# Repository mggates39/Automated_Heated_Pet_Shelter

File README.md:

# Automated Heated Pet Shelter #
This project is the software to control a heated pet shelter for my cat.

It uses an Uno, a couple of tempearture sensors, a load cell and amplifier, and a relay to activate a heating pad in the bottom of the shelter.

It uses the MyDelay Arduino library found [here](https://github.com/mggates39/MyDelay) on GitHub

Added a KiCad design for an Arduino Uno shield to interface to the sensors and relay.

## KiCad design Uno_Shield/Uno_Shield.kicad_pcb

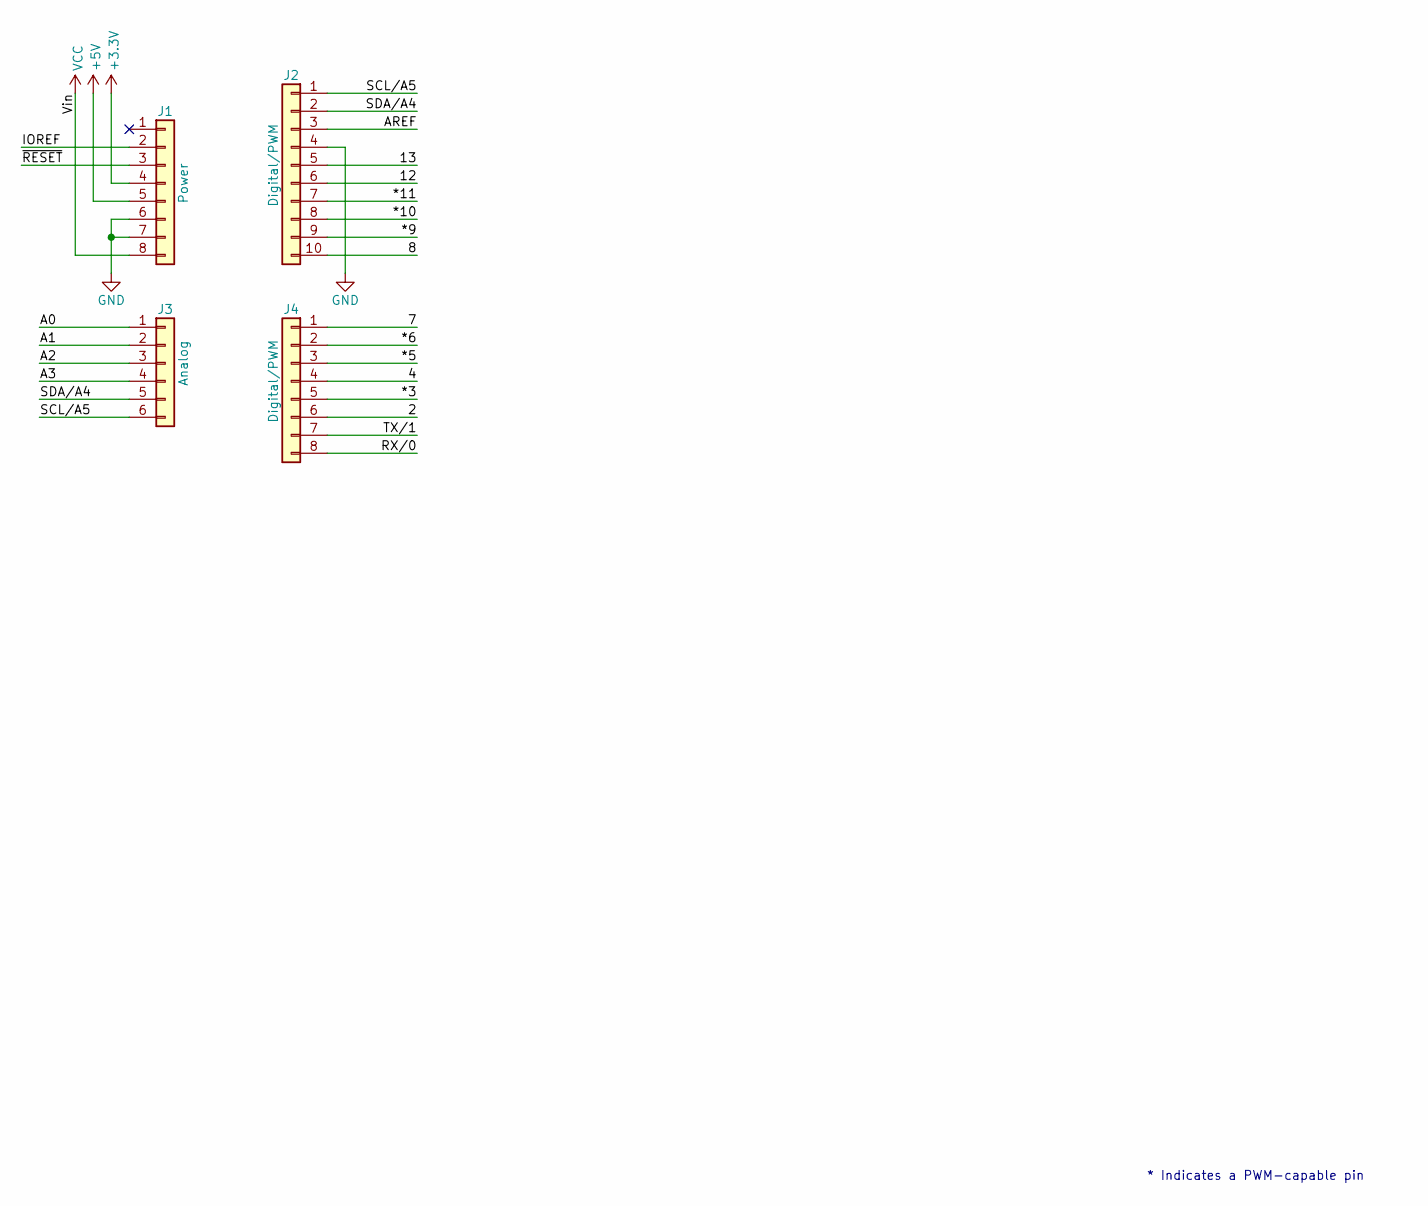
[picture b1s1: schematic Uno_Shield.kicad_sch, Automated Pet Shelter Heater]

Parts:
J1: Power; PinSocket_1x08_P2.54mm_Vertical
J2: Digital/PWM; PinSocket_1x10_P2.54mm_Vertical
J3: Analog; PinSocket_1x06_P2.54mm_Vertical
J4: Digital/PWM; PinSocket_1x08_P2.54mm_Vertical

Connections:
+3V3: J1.4
+5V: J1.5
/2: J4.6
/4: J4.4
/7: J4.1
/8: J2.10
/12: J2.6
/13: J2.5
/*3: J4.5
/*5: J4.3
/*6: J4.2
/*9: J2.9
/*10: J2.8
/*11: J2.7
/A0: J3.1
/A1: J3.2
/A2: J3.3
/A3: J3.4
/AREF: J2.3
/IOREF: J1.2
/RX/0: J4.8
/SCL/A5: J2.1, J3.6
/SDA/A4: J2.2, J3.5
/TX/1: J4.7
/~RESET: J1.3
GND: J1.6, J1.7, J2.4
VCC: J1.8

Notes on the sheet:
* Indicates a PWM-capable pin

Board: 2 copper layers, 8 parts (0 on the bottom side), 3 nets, no tracks yet.

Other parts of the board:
MH1, MH2, MH3, MH4: MountingHole_3.2mm

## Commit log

2020-12-25 Initial Commit
    Should have started this repo sooner
2020-12-26 Add the real temperature control logic
2020-12-26 Add Load Cell Support
    This will detect if a creature is in the palace
2020-12-26 Fix bug with timer values
    The caclulations were not generating longs
2020-12-28 Add support for load cell not present
    We don't have to have the load cell. Just assume we are occupied.
    Update startup display
2021-01-03 Update header comment
2021-01-03 Move some string constants to flash
2021-01-03 Update Heat Logic
    Add unoccupied heat cycle management if cold out.
    Start heat immediately when system comes on becuase of temperature
    Update Status display to use flash string helper
2021-01-07 improve graceful failure if no sensors
2021-01-09 Updated to use MyDelay library
    Removed the included additionaly files in favor or my own Arduino Library.
2021-01-10 Add support for startup mode
    Read the temperatures every 10 seconds for 5 minutes to allow them to settle down on first start up.
2021-01-10 Tighten Heat Required range
    Turn the system on at a lower temperature
2021-01-10 Add indicator on display when reading temperature
    This is because the led is not visible in the current enclosure.
2022-08-07 Added Uno Shield design
